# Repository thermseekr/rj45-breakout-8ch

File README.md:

# RJ45-BREAKOUT-8CH

Breakout board for 8x RJ45 connectors.

This board is mounted inside the automation cabinet to connect cables coming from up to eight 1-3 gang wall switch boxes, and routes those cables to an automation system.

The dimensions are such that the board can be mounted on a PCB DIN rail holder from the Brazilian manufacturer Metaltex, check [here](https://www.metaltex.com.br/produtos/componentes/suportes/sp7-suporte-para-montagem-de-placa-de-circuito-impresso-em-trilho-din) for details.

Also check [here](https://github.com/thermseekr/RJ45-breakout-1ch) for the board that mounts inside the wall switch boxes.

## VERSION HISTORY

V3 - More space saving: RJ45 jacks changed from right angle to vertical, signal connectors changed from pitch 5.08mm screw to pitch 2.54mm spring cage. Power connector changed from screw to spring cage with two poles to be able to send power to the next board.

V2 - Single power connector instead one per channel, RJ45 jacks repositioned to save space.

V1 - Initial release.

## LICENSE

This project is licensed under the [Creative Commons BY-NC 4.0 License](https://creativecommons.org/licenses/by-nc/4.0/).
Commercial use is not permitted without prior written consent. See the [LICENSE.txt](LICENSE.txt) file for details.

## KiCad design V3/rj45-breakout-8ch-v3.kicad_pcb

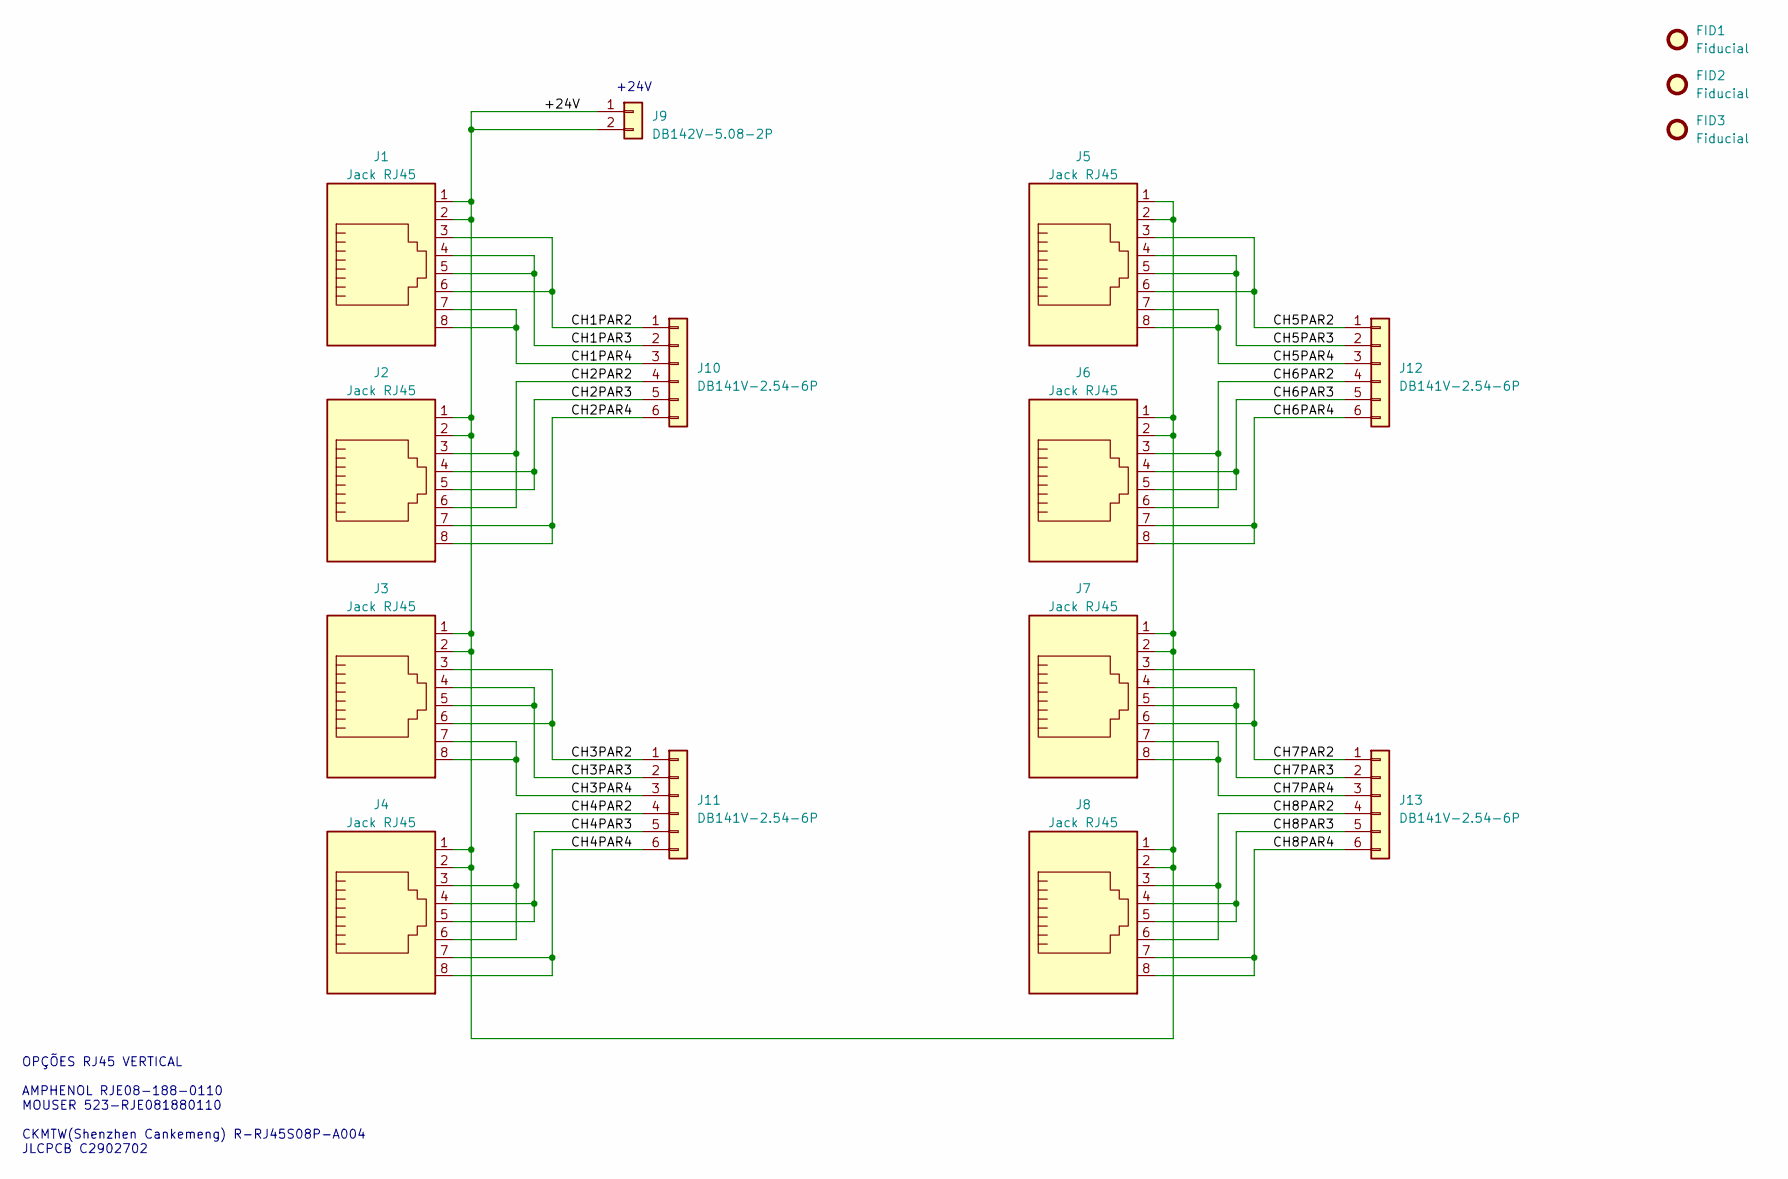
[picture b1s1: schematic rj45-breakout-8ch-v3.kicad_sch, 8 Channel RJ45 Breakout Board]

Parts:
FID1, FID2, FID3: Fiducial; Fiducial_1mm_Mask2mm
J1, J2, J3, J4, J5, J6, J7, J8: Jack RJ45; RJ45_CKMTW_R-RJ45S08P-A004; Mfr PN R-RJ45S08P-A004; JLCPCB BOM 1
J9: DB142V-5.08-2P; TerminalBlock_Dibo_DB142V-5.08-2P_1x02_P5.08mm_Vertical; Mfr PN DB142V-5.08-2P; JLCPCB BOM 1
J10, J11, J12, J13: DB141V-2.54-6P; TerminalBlock_Dibo_DB141V-2.54-6P_1x06_P2.54mm_Vertical; Mfr PN DB141V-2.54-6P; JLCPCB BOM 1

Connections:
/+24V: J1.1, J1.2, J2.1, J2.2, J3.1, J3.2, J4.1, J4.2, J5.1, J5.2, J6.1, J6.2, J7.1, J7.2, J8.1, J8.2, J9.1, J9.2
/CH1PAR2: J1.3, J1.6, J10.1
/CH1PAR3: J1.4, J1.5, J10.2
/CH1PAR4: J1.7, J1.8, J10.3
/CH2PAR2: J2.3, J2.6, J10.4
/CH2PAR3: J2.4, J2.5, J10.5
/CH2PAR4: J2.7, J2.8, J10.6
/CH3PAR2: J3.3, J3.6, J11.1
/CH3PAR3: J3.4, J3.5, J11.2
/CH3PAR4: J3.7, J3.8, J11.3
/CH4PAR2: J4.3, J4.6, J11.4
/CH4PAR3: J4.4, J4.5, J11.5
/CH4PAR4: J4.7, J4.8, J11.6
/CH5PAR2: J5.3, J5.6, J12.1
/CH5PAR3: J5.4, J5.5, J12.2
/CH5PAR4: J5.7, J5.8, J12.3
/CH6PAR2: J6.3, J6.6, J12.4
/CH6PAR3: J6.4, J6.5, J12.5
/CH6PAR4: J6.7, J6.8, J12.6
/CH7PAR2: J7.3, J7.6, J13.1
/CH7PAR3: J7.4, J7.5, J13.2
/CH7PAR4: J7.7, J7.8, J13.3
/CH8PAR2: J8.3, J8.6, J13.4
/CH8PAR3: J8.4, J8.5, J13.5
/CH8PAR4: J8.7, J8.8, J13.6

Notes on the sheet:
OPÇÕES RJ45 VERTICAL AMPHENOL RJE08-188-0110 MOUSER 523-RJE081880110 CKMTW(Shenzhen Cankemeng) R-RJ45S08P-A004 JLCPCB C2902702
+24V

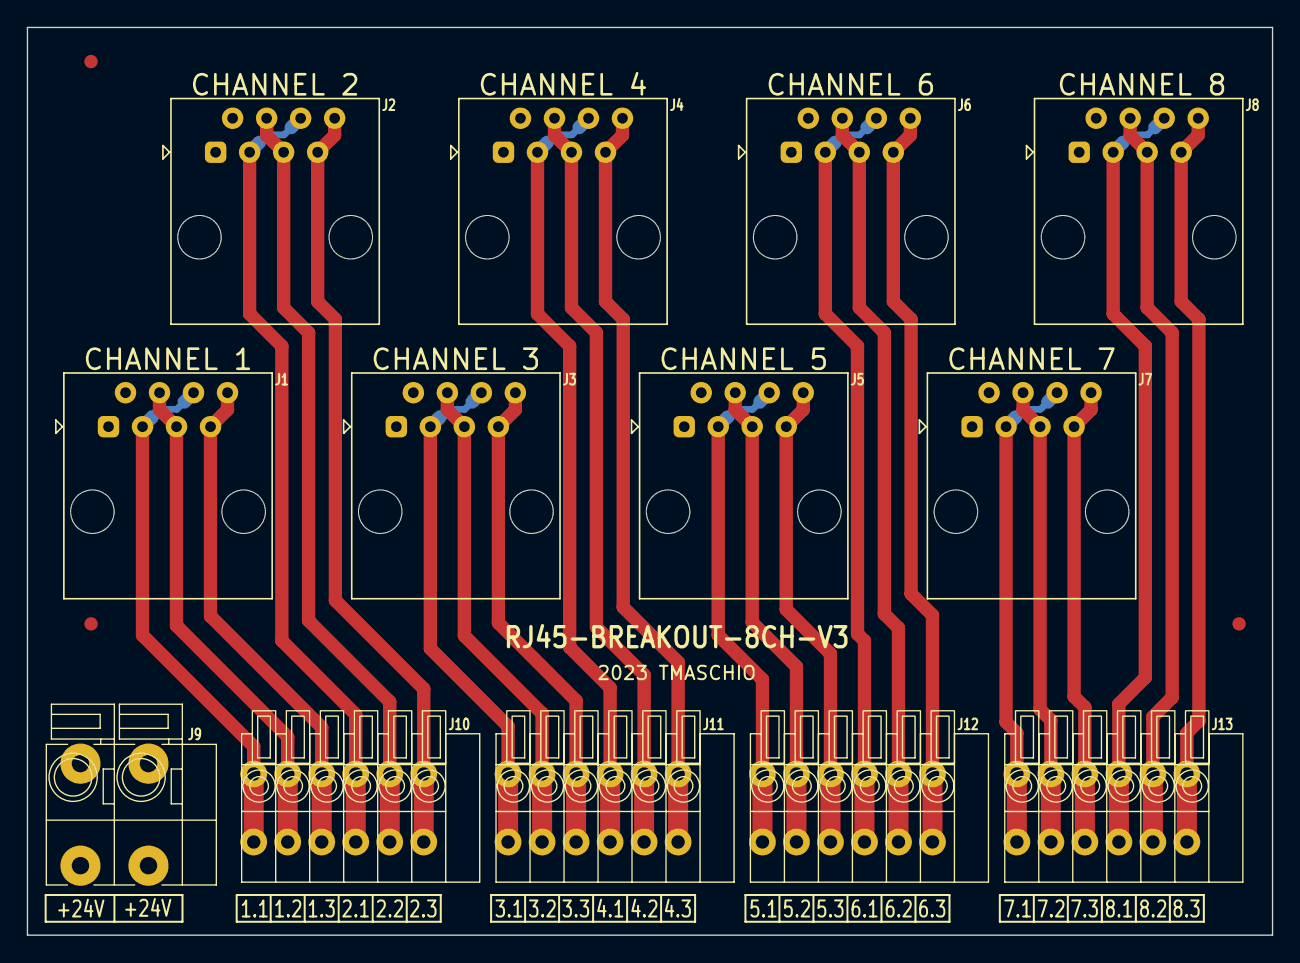
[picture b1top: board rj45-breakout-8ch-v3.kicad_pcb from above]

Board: 2 copper layers, 93.0 x 67.8 mm, 16 parts (0 on the bottom side), 25 nets.

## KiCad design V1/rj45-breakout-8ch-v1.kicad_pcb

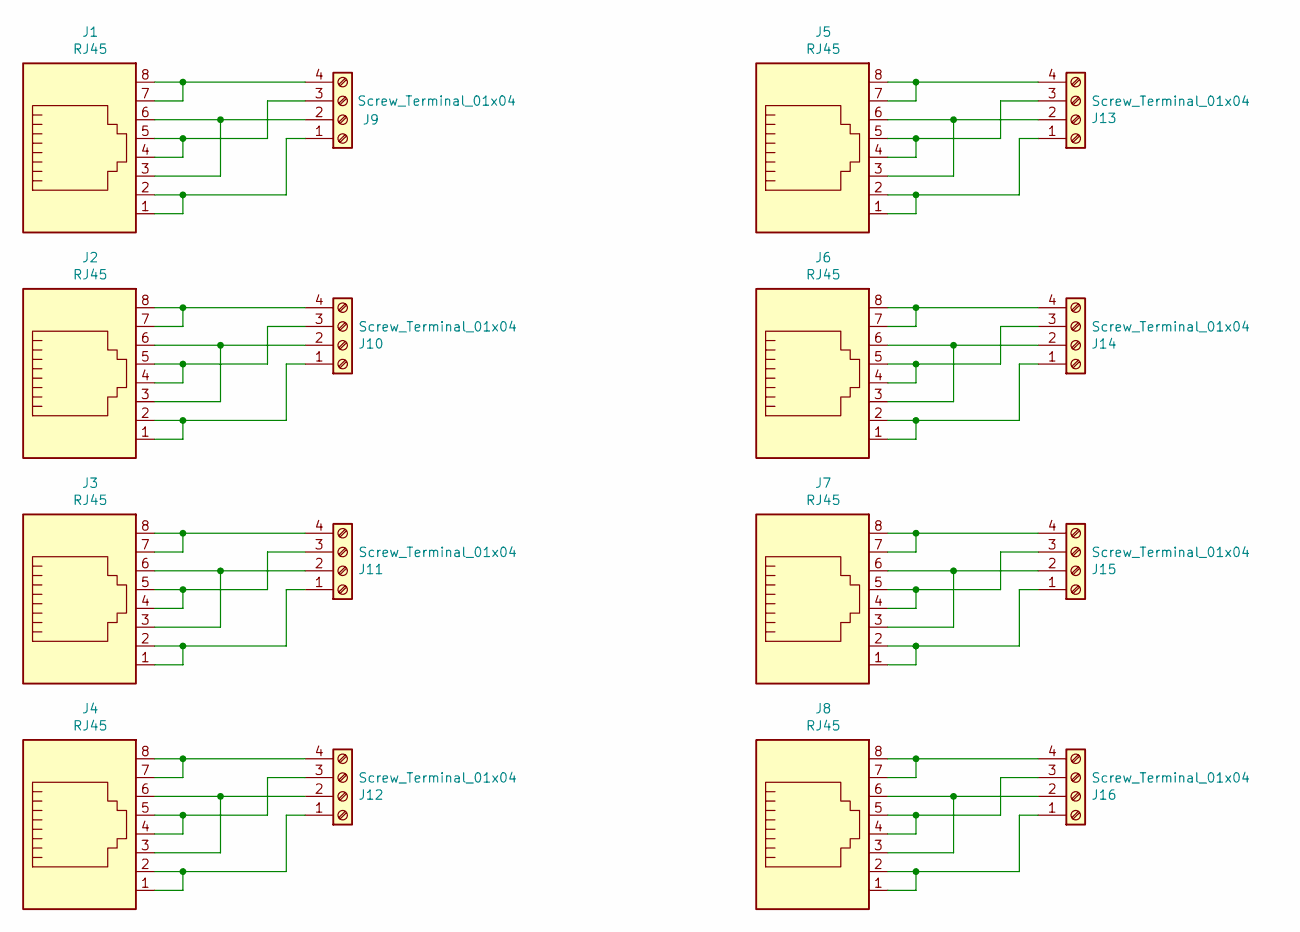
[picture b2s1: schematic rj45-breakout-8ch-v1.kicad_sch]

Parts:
J1, J2, J3, J4, J5, J6, J7, J8: RJ45; RJ45_Amphenol_RJHSE5080; Mfr PN RJHSE-5080
J9, J10, J11, J12, J13, J14, J15, J16: Screw_Terminal_01x04; TerminalBlock_Phoenix_MKDS-3-4-5.08_1x04_P5.08mm_Horizontal; Mfr PN 2x BR902V

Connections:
unnamed: J1.1, J1.2, J9.1
unnamed: J1.3, J1.6, J9.2
unnamed: J1.4, J1.5, J9.3
unnamed: J1.7, J1.8, J9.4
unnamed: J2.1, J2.2, J10.1
unnamed: J2.3, J2.6, J10.2
unnamed: J2.4, J2.5, J10.3
unnamed: J2.7, J2.8, J10.4
unnamed: J3.1, J3.2, J11.1
unnamed: J3.3, J3.6, J11.2
unnamed: J3.4, J3.5, J11.3
unnamed: J3.7, J3.8, J11.4
unnamed: J4.1, J4.2, J12.1
unnamed: J4.3, J4.6, J12.2
unnamed: J4.4, J4.5, J12.3
unnamed: J4.7, J4.8, J12.4
unnamed: J5.1, J5.2, J13.1
unnamed: J5.3, J5.6, J13.2
unnamed: J5.4, J5.5, J13.3
unnamed: J5.7, J5.8, J13.4
unnamed: J6.1, J6.2, J14.1
unnamed: J6.3, J6.6, J14.2
unnamed: J6.4, J6.5, J14.3
unnamed: J6.7, J6.8, J14.4
unnamed: J7.1, J7.2, J15.1
unnamed: J7.3, J7.6, J15.2
unnamed: J7.4, J7.5, J15.3
unnamed: J7.7, J7.8, J15.4
unnamed: J8.1, J8.2, J16.1
unnamed: J8.3, J8.6, J16.2
unnamed: J8.4, J8.5, J16.3
unnamed: J8.7, J8.8, J16.4

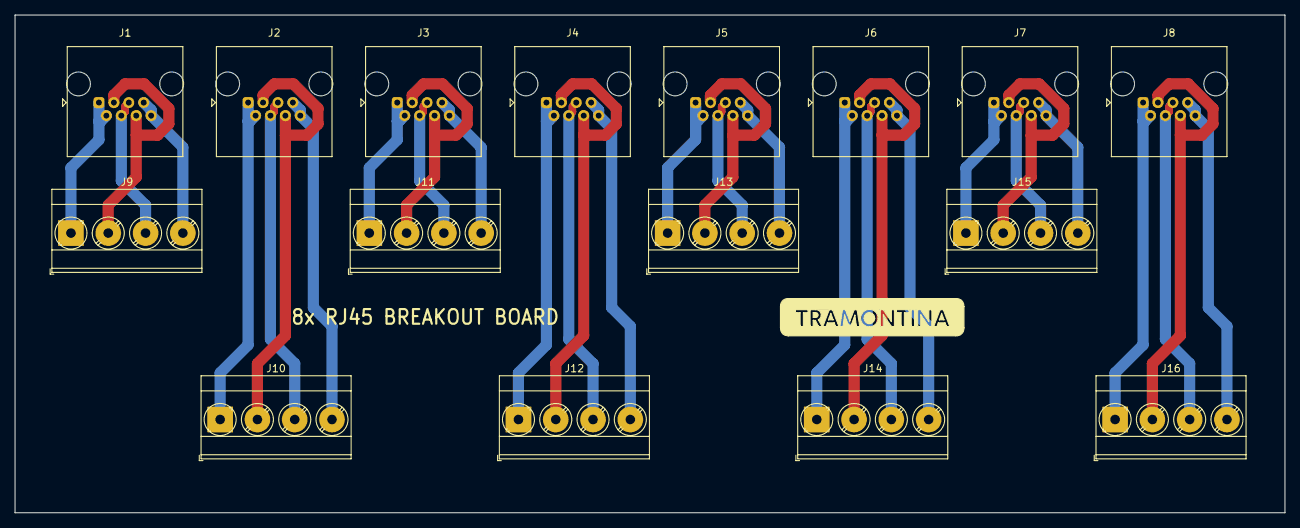
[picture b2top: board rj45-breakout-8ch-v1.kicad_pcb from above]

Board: 2 copper layers, 173.0 x 67.8 mm, 16 parts (0 on the bottom side), 32 nets.

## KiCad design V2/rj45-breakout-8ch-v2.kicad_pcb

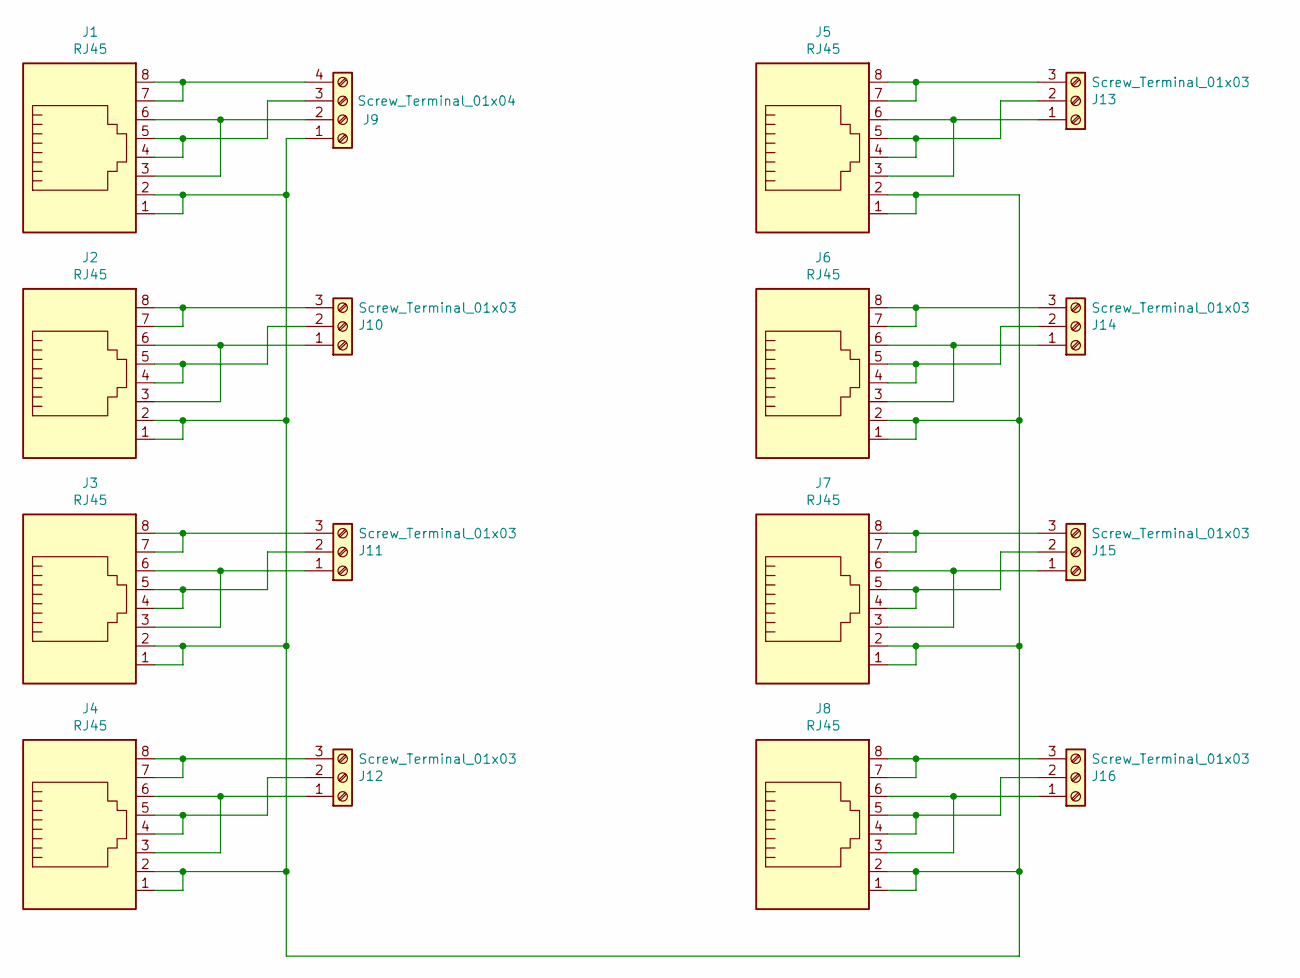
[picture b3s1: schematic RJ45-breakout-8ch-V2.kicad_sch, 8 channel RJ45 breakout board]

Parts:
J1, J2, J3, J4, J5, J6, J7, J8: RJ45; RJ45_Amphenol_RJHSE5080; Mfr PN RJHSE-5080
J9: Screw_Terminal_01x04; TerminalBlock_Phoenix_MKDS-3-4-5.08_1x04_P5.08mm_Horizontal; Mfr PN 2x BR902V
J10, J11, J12, J13, J14, J15, J16: Screw_Terminal_01x03; TerminalBlock_Phoenix_MKDS-3-3-5.08_1x03_P5.08mm_Horizontal; Mfr PN BR903V

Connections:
unnamed: J1.1, J1.2, J2.1, J2.2, J3.1, J3.2, J4.1, J4.2, J5.1, J5.2, J6.1, J6.2, J7.1, J7.2, J8.1, J8.2, J9.1
unnamed: J1.3, J1.6, J9.2
unnamed: J1.4, J1.5, J9.3
unnamed: J1.7, J1.8, J9.4
unnamed: J2.3, J2.6, J10.1
unnamed: J2.4, J2.5, J10.2
unnamed: J2.7, J2.8, J10.3
unnamed: J3.3, J3.6, J11.1
unnamed: J3.4, J3.5, J11.2
unnamed: J3.7, J3.8, J11.3
unnamed: J4.3, J4.6, J12.1
unnamed: J4.4, J4.5, J12.2
unnamed: J4.7, J4.8, J12.3
unnamed: J5.3, J5.6, J13.1
unnamed: J5.4, J5.5, J13.2
unnamed: J5.7, J5.8, J13.3
unnamed: J6.3, J6.6, J14.1
unnamed: J6.4, J6.5, J14.2
unnamed: J6.7, J6.8, J14.3
unnamed: J7.3, J7.6, J15.1
unnamed: J7.4, J7.5, J15.2
unnamed: J7.7, J7.8, J15.3
unnamed: J8.3, J8.6, J16.1
unnamed: J8.4, J8.5, J16.2
unnamed: J8.7, J8.8, J16.3

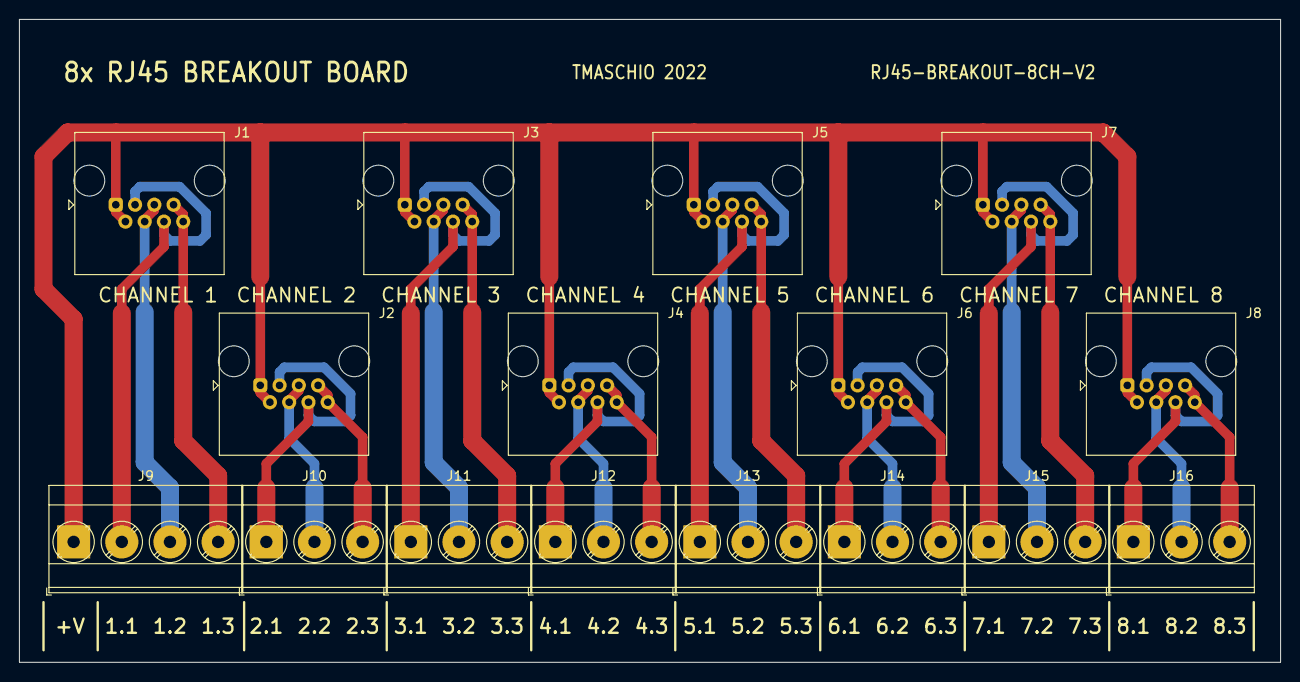
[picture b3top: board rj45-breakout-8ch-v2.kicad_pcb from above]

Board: 2 copper layers, 133.0 x 67.8 mm, 16 parts (0 on the bottom side), 25 nets.

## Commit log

2022-02-02 Initial upload
2022-02-05 updates to components
2022-02-17 design review
2022-02-28 Cleanup after migration to Kicad 6
2022-03-29 work in progress
2022-04-01 PCB tweaks
2022-04-03 rename files to new schema
2022-04-04 Backup
2022-04-12 backups
2023-04-27 Refresh
2023-05-21 Update board image
2023-06-22 Update V1 Kicad version
2023-08-06 Part numbers update
2023-08-11 Added information on RJ45 connectors
2023-08-19 Connectors rotated 180deg
2023-08-21 Added text regarding RJ45 connectors
2023-08-21 Repository reorg and cleanup
2023-08-22 Layout tweakings
2023-08-23 Footprints updated
2023-08-23 Grid changed to mm
2023-08-24 Align parts and tracks to mm grid
2023-08-24 Move to mm grid
2023-08-26 Cosmetic enhancements to PCB
2023-09-05 New image
2023-09-06 Renaming to lowercase
2024-10-02 Update to Kicad 8
2024-11-06 Update to Kicad V8
2024-11-23 Update components
2025-04-14 Prefab checks
2025-05-27 Something
2025-06-30 Added license
2025-11-27 Kicad version update
2025-12-09 Revision for manufacturing
2025-12-10 Small updates before fabrication
2025-12-10 Revising before production
2025-12-11 Revising for fabrication
